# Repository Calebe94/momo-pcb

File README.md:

# Momo Keyboard - PCB

This keyboard is inspired by [Appa](https://github.com/Calebe94/appa-pcb).

# License

All software is covered under [GNU General Public License v3.0](https://www.gnu.org/licenses/gpl-3.0.en.html).

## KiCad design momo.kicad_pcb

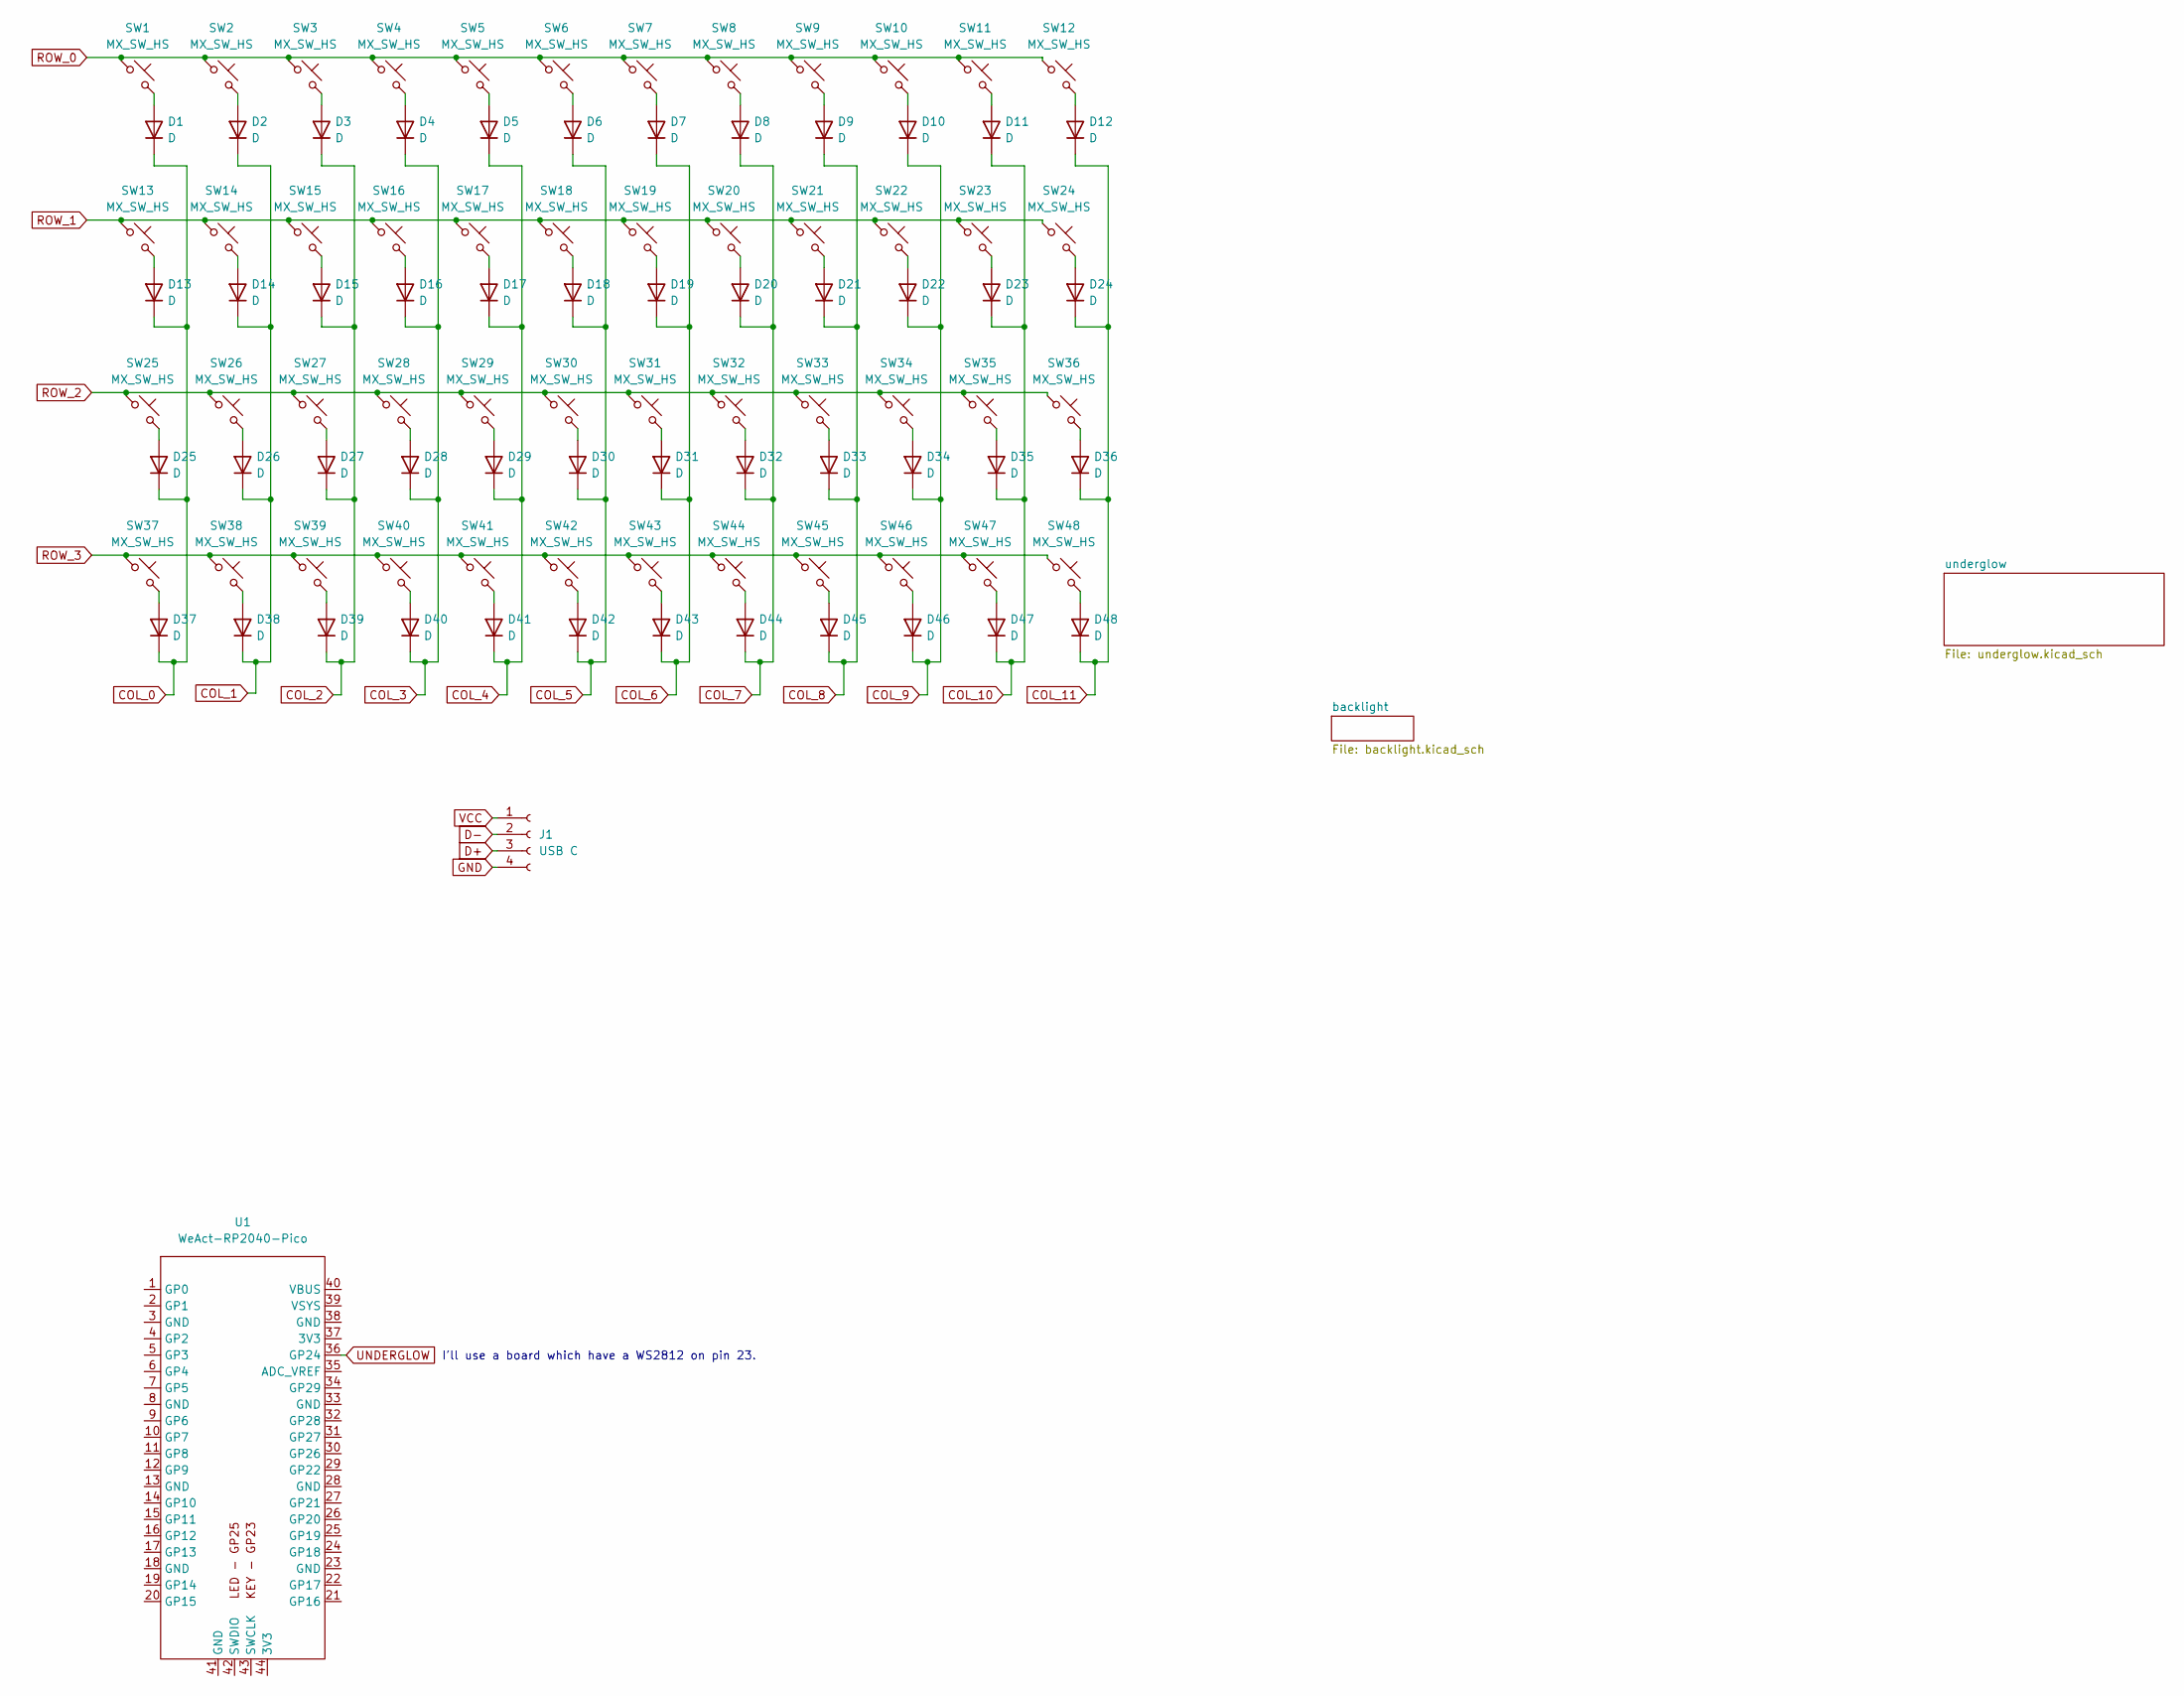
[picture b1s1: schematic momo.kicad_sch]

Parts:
D1, D2, D3, D4, D5, D6, D7, D8, D9, D10, D11, D12, D13, D14, D15, D16, D17, D18, D19, D20, D21, D22, D23, D24, D25, D26, D27, D28, D29, D30, D31, D32, D33, D34, D35, D36, D37, D38, D39, D40, D41, D42, D43, D44, D45, D46, D47, D48: D; D_SOD123_axial
J1: USB C; PinHeader_1x04_P2.54mm_Vertical
SW1, SW2, SW3, SW4, SW5, SW6, SW7, SW8, SW9, SW10, SW11, SW12, SW13, SW14, SW15, SW16, SW17, SW18, SW19, SW20, SW21, SW22, SW23, SW24, SW25, SW26, SW27, SW28, SW29, SW30, SW31, SW32, SW33, SW34, SW35, SW36, SW37, SW38, SW39, SW40, SW41, SW42, SW43, SW44, SW45, SW46, SW47, SW48: MX_SW_HS; SW_MX_HS_1u
U1: WeAct-RP2040-Pico

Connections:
COL_0: D1.1 (K), D13.1 (K), D25.1 (K), D37.1 (K)
COL_1: D2.1 (K), D14.1 (K), D26.1 (K), D38.1 (K)
COL_2: D3.1 (K), D15.1 (K), D27.1 (K), D39.1 (K)
COL_3: D4.1 (K), D16.1 (K), D28.1 (K), D40.1 (K)
COL_4: D5.1 (K), D17.1 (K), D29.1 (K), D41.1 (K)
COL_5: D6.1 (K), D18.1 (K), D30.1 (K), D42.1 (K)
COL_6: D7.1 (K), D19.1 (K), D31.1 (K), D43.1 (K)
COL_7: D8.1 (K), D20.1 (K), D32.1 (K), D44.1 (K)
COL_8: D9.1 (K), D21.1 (K), D33.1 (K), D45.1 (K)
COL_9: D10.1 (K), D22.1 (K), D34.1 (K), D46.1 (K)
COL_10: D11.1 (K), D23.1 (K), D35.1 (K), D47.1 (K)
COL_11: D12.1 (K), D24.1 (K), D36.1 (K), D48.1 (K)
D+: J1.3
D-: J1.2
GND: J1.4; also elsewhere on the board
unnamed: D1.2 (A), SW1.2
unnamed: D2.2 (A), SW2.2
unnamed: D3.2 (A), SW3.2
unnamed: D4.2 (A), SW4.2
unnamed: D5.2 (A), SW5.2
unnamed: D6.2 (A), SW6.2
unnamed: D7.2 (A), SW7.2
unnamed: D8.2 (A), SW8.2
unnamed: D9.2 (A), SW9.2
unnamed: D10.2 (A), SW10.2
unnamed: D11.2 (A), SW11.2
unnamed: D12.2 (A), SW12.2
unnamed: D13.2 (A), SW13.2
unnamed: D14.2 (A), SW14.2
unnamed: D15.2 (A), SW15.2
unnamed: D16.2 (A), SW16.2
unnamed: D17.2 (A), SW17.2
unnamed: D18.2 (A), SW18.2
unnamed: D19.2 (A), SW19.2
unnamed: D20.2 (A), SW20.2
unnamed: D21.2 (A), SW21.2
unnamed: D22.2 (A), SW22.2
unnamed: D23.2 (A), SW23.2
unnamed: D24.2 (A), SW24.2
unnamed: D25.2 (A), SW25.2
unnamed: D26.2 (A), SW26.2
unnamed: D27.2 (A), SW27.2
unnamed: D28.2 (A), SW28.2
unnamed: D29.2 (A), SW29.2
unnamed: D30.2 (A), SW30.2
unnamed: D31.2 (A), SW31.2
unnamed: D32.2 (A), SW32.2
unnamed: D33.2 (A), SW33.2
unnamed: D34.2 (A), SW34.2
unnamed: D35.2 (A), SW35.2
unnamed: D36.2 (A), SW36.2
unnamed: D37.2 (A), SW37.2
unnamed: D38.2 (A), SW38.2
unnamed: D39.2 (A), SW39.2
unnamed: D40.2 (A), SW40.2
unnamed: D41.2 (A), SW41.2
unnamed: D42.2 (A), SW42.2
unnamed: D43.2 (A), SW43.2
unnamed: D44.2 (A), SW44.2
unnamed: D45.2 (A), SW45.2
unnamed: D46.2 (A), SW46.2
unnamed: D47.2 (A), SW47.2
unnamed: D48.2 (A), SW48.2
ROW_0: SW1.1, SW2.1, SW3.1, SW4.1, SW5.1, SW6.1, SW7.1, SW8.1, SW9.1, SW10.1, SW11.1, SW12.1
ROW_1: SW13.1, SW14.1, SW15.1, SW16.1, SW17.1, SW18.1, SW19.1, SW20.1, SW21.1, SW22.1, SW23.1, SW24.1
ROW_2: SW25.1, SW26.1, SW27.1, SW28.1, SW29.1, SW30.1, SW31.1, SW32.1, SW33.1, SW34.1, SW35.1, SW36.1
ROW_3: SW37.1, SW38.1, SW39.1, SW40.1, SW41.1, SW42.1, SW43.1, SW44.1, SW45.1, SW46.1, SW47.1, SW48.1
UNDERGLOW: U1.36 (GP24); also elsewhere on the board
VCC: J1.1; also elsewhere on the board

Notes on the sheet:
I'll use a board which have a WS2812 on pin 23.

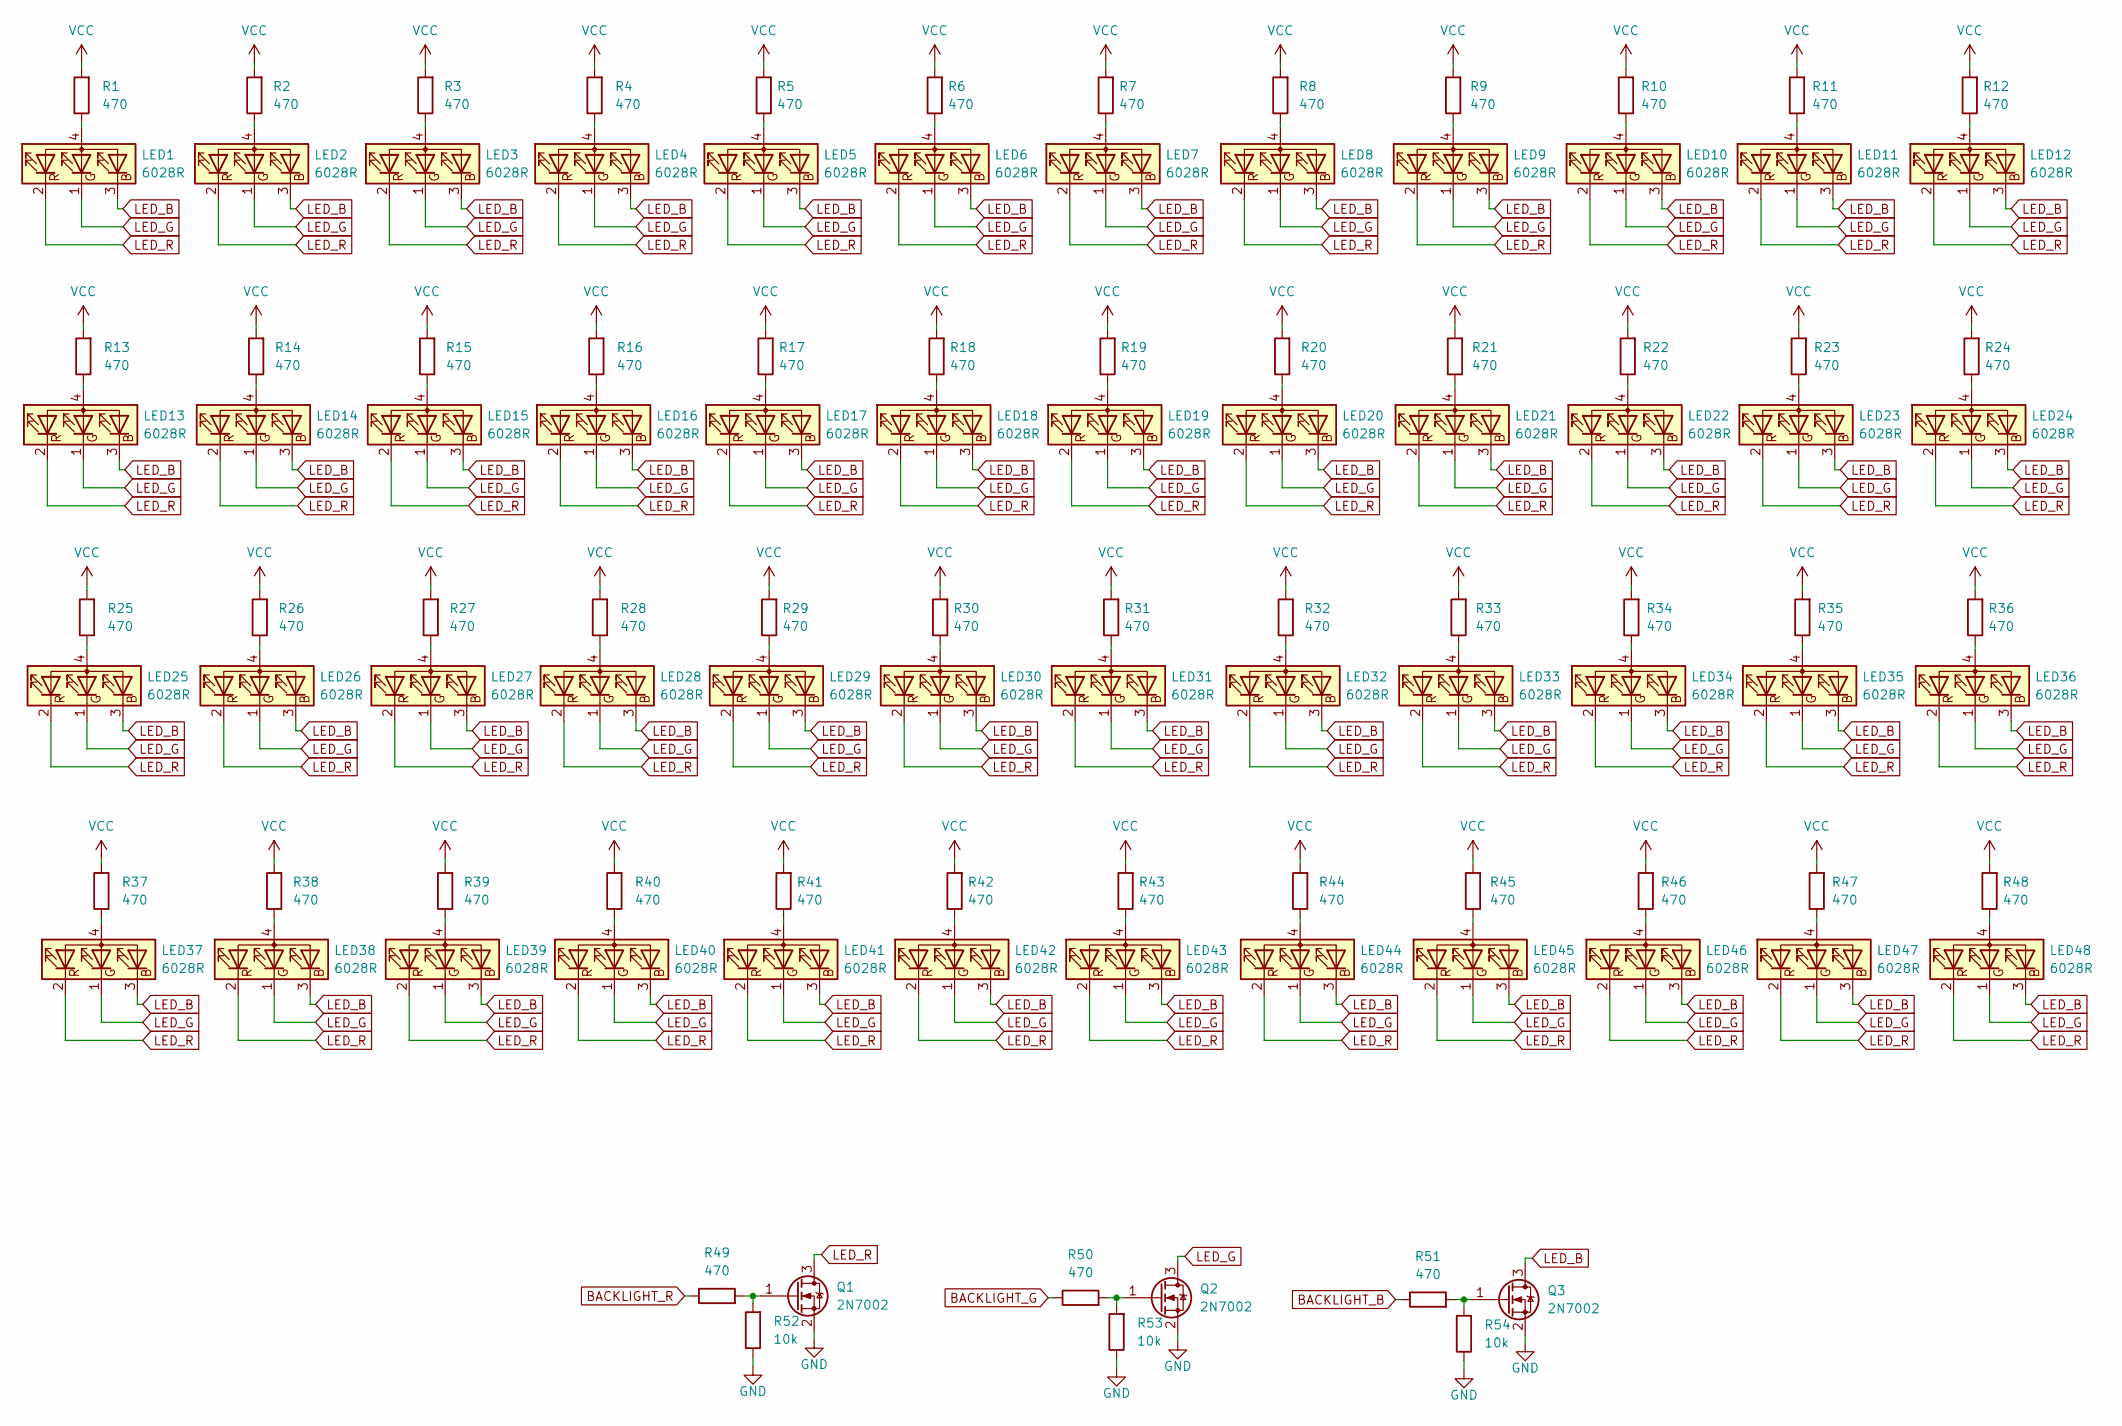
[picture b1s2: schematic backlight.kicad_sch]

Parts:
LED1, LED2, LED3, LED4, LED5, LED6, LED7, LED8, LED9, LED10, LED11, LED12, LED13, LED14, LED15, LED16, LED17, LED18, LED19, LED20, LED21, LED22, LED23, LED24, LED25, LED26, LED27, LED28, LED29, LED30, LED31, LED32, LED33, LED34, LED35, LED36, LED37, LED38, LED39, LED40, LED41, LED42, LED43, LED44, LED45, LED46, LED47, LED48: 6028R; LED_MX_6028R
Q1, Q2, Q3: 2N7002; SOT-23
R1, R2, R3, R4, R5, R6, R7, R8, R9, R10, R11, R12, R13, R14, R15, R16, R17, R18, R19, R20, R21, R22, R23, R24, R25, R26, R27, R28, R29, R30, R31, R32, R33, R34, R35, R36, R37, R38, R39, R40, R41, R42, R43, R44, R45, R46, R47, R48, R49, R50, R51: 470; R_Axial_DIN0204_L3.6mm_D1.6mm_P7.62mm_Horizontal
R52, R53, R54: 10k; R_Axial_DIN0204_L3.6mm_D1.6mm_P7.62mm_Horizontal

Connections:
BACKLIGHT_B: R51.1
BACKLIGHT_G: R50.1
BACKLIGHT_R: R49.1
GND: Q1.2 (S), Q2.2 (S), Q3.2 (S), R52.1, R53.1, R54.1; also elsewhere on the board
LED_B: LED1.3 (BK), LED2.3 (BK), LED3.3 (BK), LED4.3 (BK), LED5.3 (BK), LED6.3 (BK), LED7.3 (BK), LED8.3 (BK), LED9.3 (BK), LED10.3 (BK), LED11.3 (BK), LED12.3 (BK), LED13.3 (BK), LED14.3 (BK), LED15.3 (BK), LED16.3 (BK), LED17.3 (BK), LED18.3 (BK), LED19.3 (BK), LED20.3 (BK), LED21.3 (BK), LED22.3 (BK), LED23.3 (BK), LED24.3 (BK), LED25.3 (BK), LED26.3 (BK), LED27.3 (BK), LED28.3 (BK), LED29.3 (BK), LED30.3 (BK), LED31.3 (BK), LED32.3 (BK), LED33.3 (BK), LED34.3 (BK), LED35.3 (BK), LED36.3 (BK), LED37.3 (BK), LED38.3 (BK), LED39.3 (BK), LED40.3 (BK), LED41.3 (BK), LED42.3 (BK), LED43.3 (BK), LED44.3 (BK), LED45.3 (BK), LED46.3 (BK), LED47.3 (BK), LED48.3 (BK), Q3.3 (D)
LED_G: LED1.1 (GK), LED2.1 (GK), LED3.1 (GK), LED4.1 (GK), LED5.1 (GK), LED6.1 (GK), LED7.1 (GK), LED8.1 (GK), LED9.1 (GK), LED10.1 (GK), LED11.1 (GK), LED12.1 (GK), LED13.1 (GK), LED14.1 (GK), LED15.1 (GK), LED16.1 (GK), LED17.1 (GK), LED18.1 (GK), LED19.1 (GK), LED20.1 (GK), LED21.1 (GK), LED22.1 (GK), LED23.1 (GK), LED24.1 (GK), LED25.1 (GK), LED26.1 (GK), LED27.1 (GK), LED28.1 (GK), LED29.1 (GK), LED30.1 (GK), LED31.1 (GK), LED32.1 (GK), LED33.1 (GK), LED34.1 (GK), LED35.1 (GK), LED36.1 (GK), LED37.1 (GK), LED38.1 (GK), LED39.1 (GK), LED40.1 (GK), LED41.1 (GK), LED42.1 (GK), LED43.1 (GK), LED44.1 (GK), LED45.1 (GK), LED46.1 (GK), LED47.1 (GK), LED48.1 (GK), Q2.3 (D)
LED_R: LED1.2 (RK), LED2.2 (RK), LED3.2 (RK), LED4.2 (RK), LED5.2 (RK), LED6.2 (RK), LED7.2 (RK), LED8.2 (RK), LED9.2 (RK), LED10.2 (RK), LED11.2 (RK), LED12.2 (RK), LED13.2 (RK), LED14.2 (RK), LED15.2 (RK), LED16.2 (RK), LED17.2 (RK), LED18.2 (RK), LED19.2 (RK), LED20.2 (RK), LED21.2 (RK), LED22.2 (RK), LED23.2 (RK), LED24.2 (RK), LED25.2 (RK), LED26.2 (RK), LED27.2 (RK), LED28.2 (RK), LED29.2 (RK), LED30.2 (RK), LED31.2 (RK), LED32.2 (RK), LED33.2 (RK), LED34.2 (RK), LED35.2 (RK), LED36.2 (RK), LED37.2 (RK), LED38.2 (RK), LED39.2 (RK), LED40.2 (RK), LED41.2 (RK), LED42.2 (RK), LED43.2 (RK), LED44.2 (RK), LED45.2 (RK), LED46.2 (RK), LED47.2 (RK), LED48.2 (RK), Q1.3 (D)
unnamed: LED1.4 (A), R1.1
unnamed: LED2.4 (A), R2.1
unnamed: LED3.4 (A), R3.1
unnamed: LED4.4 (A), R4.1
unnamed: LED5.4 (A), R5.1
unnamed: LED6.4 (A), R6.1
unnamed: LED7.4 (A), R7.1
unnamed: LED8.4 (A), R8.1
unnamed: LED9.4 (A), R9.1
unnamed: LED10.4 (A), R10.1
unnamed: LED11.4 (A), R11.1
unnamed: LED12.4 (A), R12.1
unnamed: LED13.4 (A), R13.1
unnamed: LED14.4 (A), R14.1
unnamed: LED15.4 (A), R15.1
unnamed: LED16.4 (A), R16.1
unnamed: LED17.4 (A), R17.1
unnamed: LED18.4 (A), R18.1
unnamed: LED19.4 (A), R19.1
unnamed: LED20.4 (A), R20.1
unnamed: LED21.4 (A), R21.1
unnamed: LED22.4 (A), R22.1
unnamed: LED23.4 (A), R23.1
unnamed: LED24.4 (A), R24.1
unnamed: LED25.4 (A), R25.1
unnamed: LED26.4 (A), R26.1
unnamed: LED27.4 (A), R27.1
unnamed: LED28.4 (A), R28.1
unnamed: LED29.4 (A), R29.1
unnamed: LED30.4 (A), R30.1
unnamed: LED31.4 (A), R31.1
unnamed: LED32.4 (A), R32.1
unnamed: LED33.4 (A), R33.1
unnamed: LED34.4 (A), R34.1
unnamed: LED35.4 (A), R35.1
unnamed: LED36.4 (A), R36.1
unnamed: LED37.4 (A), R37.1
unnamed: LED38.4 (A), R38.1
unnamed: LED39.4 (A), R39.1
unnamed: LED40.4 (A), R40.1
unnamed: LED41.4 (A), R41.1
unnamed: LED42.4 (A), R42.1
unnamed: LED43.4 (A), R43.1
unnamed: LED44.4 (A), R44.1
unnamed: LED45.4 (A), R45.1
unnamed: LED46.4 (A), R46.1
unnamed: LED47.4 (A), R47.1
unnamed: LED48.4 (A), R48.1
unnamed: Q1.1 (G), R49.2, R52.2
unnamed: Q2.1 (G), R50.2, R53.2
unnamed: Q3.1 (G), R51.2, R54.2
VCC: R1.2, R2.2, R3.2, R4.2, R5.2, R6.2, R7.2, R8.2, R9.2, R10.2, R11.2, R12.2, R13.2, R14.2, R15.2, R16.2, R17.2, R18.2, R19.2, R20.2, R21.2, R22.2, R23.2, R24.2, R25.2, R26.2, R27.2, R28.2, R29.2, R30.2, R31.2, R32.2, R33.2, R34.2, R35.2, R36.2, R37.2, R38.2, R39.2, R40.2, R41.2, R42.2, R43.2, R44.2, R45.2, R46.2, R47.2, R48.2; also elsewhere on the board

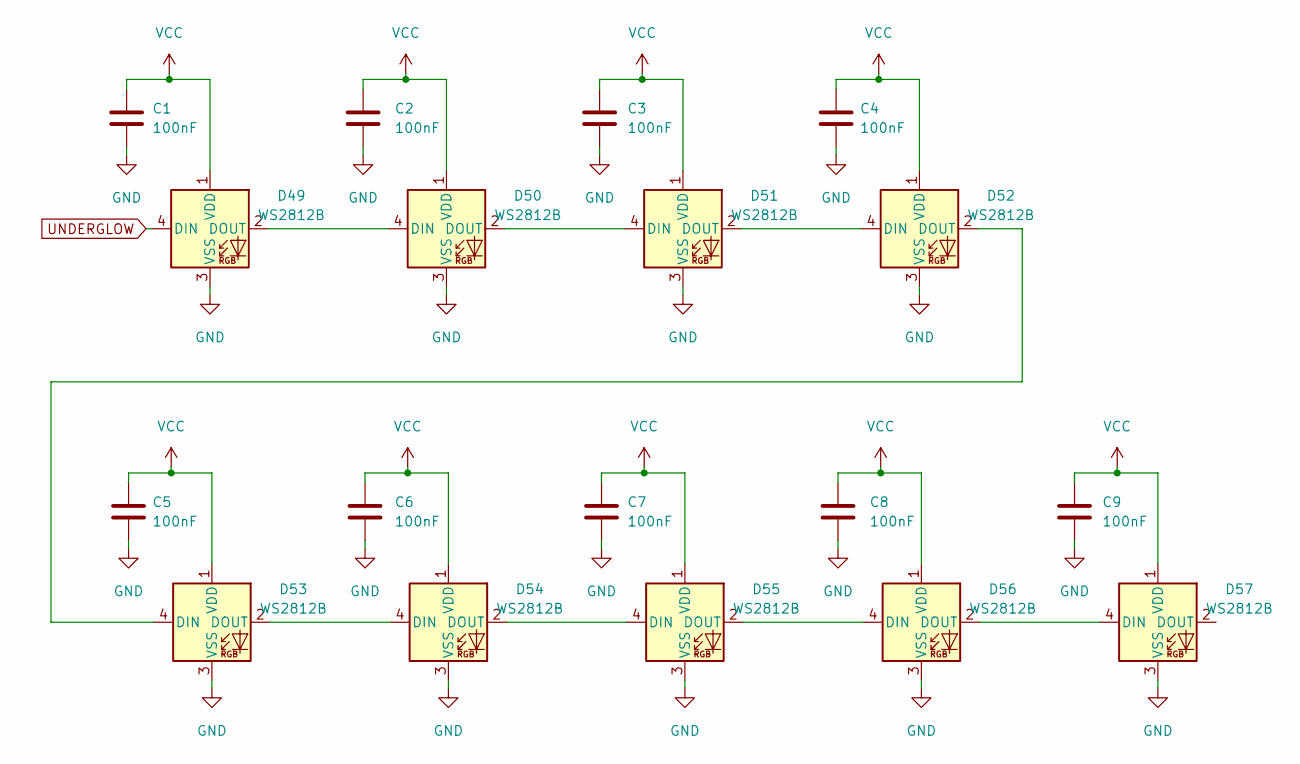
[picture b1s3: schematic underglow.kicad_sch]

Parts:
C1, C2, C3, C4, C5, C6, C7, C8, C9: 100nF; C_1608
D49, D50, D51, D52, D53, D54, D55, D56, D57: WS2812B; LED_WS2812B_PLCC4_5.0x5.0mm_P3.2mm

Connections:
GND: C1.2, C2.2, C3.2, C4.2, C5.2, C6.2, C7.2, C8.2, C9.2, D49.3 (VSS), D50.3 (VSS), D51.3 (VSS), D52.3 (VSS), D53.3 (VSS), D54.3 (VSS), D55.3 (VSS), D56.3 (VSS), D57.3 (VSS); also elsewhere on the board
unnamed: D49.2 (DOUT), D50.4 (DIN)
unnamed: D50.2 (DOUT), D51.4 (DIN)
unnamed: D51.2 (DOUT), D52.4 (DIN)
unnamed: D52.2 (DOUT), D53.4 (DIN)
unnamed: D53.2 (DOUT), D54.4 (DIN)
unnamed: D54.2 (DOUT), D55.4 (DIN)
unnamed: D55.2 (DOUT), D56.4 (DIN)
unnamed: D56.2 (DOUT), D57.4 (DIN)
UNDERGLOW: D49.4 (DIN); also elsewhere on the board
VCC: C1.1, C2.1, C3.1, C4.1, C5.1, C6.1, C7.1, C8.1, C9.1, D49.1 (VDD), D50.1 (VDD), D51.1 (VDD), D52.1 (VDD), D53.1 (VDD), D54.1 (VDD), D55.1 (VDD), D56.1 (VDD), D57.1 (VDD); also elsewhere on the board

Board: 2 copper layers, 221 parts (0 on the bottom side), 129 nets, no tracks yet.

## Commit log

2023-06-02 Added RGB underglow functionality
2023-06-02 Routed components
2023-06-02 Added RGB backlight functionality
2023-06-02 Pin wiring
2023-06-02 Added i2c pins
